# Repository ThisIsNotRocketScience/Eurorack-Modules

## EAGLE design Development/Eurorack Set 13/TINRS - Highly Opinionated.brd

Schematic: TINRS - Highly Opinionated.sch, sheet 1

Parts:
C1, C9, C15, C16, C20, C23, C24, C25, C26, C27: 3.3nF; C0603
C17, C22, C28: 100nF; C0603; MPN MC0603F104Z160CT
D5: yellow; 3MMLED
IC2, IC4, IC5: MCP6004; SO14; MPN MCP6004-I/SL.
J1, J2, J3, J4, J5, J6, J9, J15, J16, J17, J18, J19: PJ-341; 3.5MM-JACK-SWITCH-13MM-INPUT
Q1, Q2: MMBT3904; SOT23-BEC; MPN PMBT3904,215
R1, R11, R13, R14, R16, R18, R65, R76, R81, R86, R91, R96: 100k; R0603
R2, R12, R22, R23, R27, R30, R39, R41, R66, R72, R75, R82, R84, R87, R89, R92, R94, R97, R99: 33k; R0603
R3, R15, R28, R40, R71, R77, R83, R88, R93, R98: 51k; R0603
R17, R29, R68, R69, R70, R73, R85, R90, R95: 10kB; ALPS_POT_SQUAREHOLES
R20, R42: 10k; R0603
R74: 56; R0603

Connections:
3.3V: C17.1, C22.1, C28.1, IC2.4 (V+), IC4.4 (V+), IC5.4 (V+), R17.P$3 (A), R20.2, R29.P$3 (A), R42.2, R68.P$3 (A), R69.P$3 (A), R70.P$3 (A), R73.P$3 (A), R85.P$3 (A), R90.P$3 (A), R95.P$3 (A); also elsewhere on the board
12V: J9.SWITCH@3 (SWITCH); also elsewhere on the board
ADC_ATTACK: C9.2, IC4.7 (OUT), R66.1
ADC_CURVE: C20.2, IC2.1 (OUT), R39.1
ADC_CVADJUST: C24.2, C25.2, C26.2, C27.2, IC5.1 (OUT), IC5.7 (OUT), IC5.8 (OUT), IC5.14 (OUT), R82.1, R87.1, R92.1, R97.1
ADC_DECAY: C16.2, IC4.14 (OUT), R22.1
ADC_RELEASE: C1.2, IC4.1 (OUT), R2.1
ADC_SUSTAIN: C15.2, IC4.8 (OUT), R12.1
ADC_VELOCITY: C23.2, IC2.8 (OUT), R75.1
EXTCV: J16.SWITCH@3 (SWITCH); also elsewhere on the board
EXTGATE: J5.SWITCH@3 (SWITCH); also elsewhere on the board
GND: C17.2, C22.2, C28.2, D5.-, IC2.3 (+IN), IC2.10 (+IN), IC2.11 (V-), IC2.12 (+IN), IC4.3 (+IN), IC4.5 (+IN), IC4.10 (+IN), IC4.11 (V-), IC4.12 (+IN), IC5.3 (+IN), IC5.5 (+IN), IC5.10 (+IN), IC5.11 (V-), IC5.12 (+IN), J1.RING@3 (RING), J1.SWITCH@3 (SWITCH), J2.RING@3 (RING), J2.SWITCH@3 (SWITCH), J3.RING@3 (RING), J3.SWITCH@3 (SWITCH), J4.RING@3 (RING), J4.SWITCH@3 (SWITCH), J5.RING@3 (RING), J6.RING@3 (RING), J6.SWITCH@3 (SWITCH), J9.RING@3 (RING), J15.RING@3 (RING), J15.SWITCH@3 (SWITCH), J16.RING@3 (RING), J17.RING@3 (RING), J17.SWITCH@3 (SWITCH), J18.RING@3 (RING), J18.SWITCH@3 (SWITCH), J19.RING@3 (RING), J19.SWITCH@3 (SWITCH), Q1.E, Q2.E, R17.P$1 (E), R29.P$1 (E), R68.P$1 (E), R69.P$1 (E), R70.P$1 (E), R73.P$1 (E), R85.P$1 (E), R90.P$1 (E), R95.P$1 (E); also elsewhere on the board
KNOB_ATTACK: R72.2, R73.P$2 (S)
KNOB_CURVE: R41.2, R70.P$2 (S)
KNOB_CVADJUST: R29.P$2 (S), R84.2
KNOB_DECAY: R17.P$2 (S), R30.2
KNOB_INSTRUMENT: R95.P$2 (S), R99.2
KNOB_PERSONALITY: R85.P$2 (S), R89.2
KNOB_RELEASE: R27.2, R69.P$2 (S)
KNOB_SKILL: R90.P$2 (S), R94.2
KNOB_SUSTAIN: R23.2, R68.P$2 (S)
unnamed: J2.TIP@3 (TIP), R16.2
unnamed: C15.1, IC4.9 (-IN), R12.2, R15.1, R16.1, R23.1
unnamed: J3.TIP@3 (TIP), R1.2
unnamed: C1.1, IC4.2 (-IN), R1.1, R2.2, R3.1, R27.1
unnamed: J16.TIP@3 (TIP), R81.2
unnamed: C24.1, IC5.2 (-IN), R81.1, R82.2, R83.1, R84.1
unnamed: J15.TIP@3 (TIP), R65.2
unnamed: J4.TIP@3 (TIP), R13.2
unnamed: Q1.B, R18.2
unnamed: J5.TIP@3 (TIP), R18.1
unnamed: IC2.6 (-IN), IC2.7 (OUT), R74.2
unnamed: C9.1, IC4.6 (-IN), R65.1, R66.2, R71.1, R72.1
unnamed: IC2.13 (-IN), IC2.14 (OUT)
unnamed: J1.TIP@3 (TIP), R14.2
unnamed: C16.1, IC4.13 (-IN), R14.1, R22.2, R28.1, R30.1
unnamed: Q2.B, R11.2
unnamed: C20.1, IC2.2 (-IN), R13.1, R39.2, R40.1, R41.1
unnamed: J6.TIP@3 (TIP), R11.1
unnamed: C23.1, IC2.9 (-IN), R75.2, R76.1, R77.1
unnamed: D5.+, R74.1
unnamed: J17.TIP@3 (TIP), R86.2
unnamed: J9.TIP@3 (TIP), R76.2
unnamed: C25.1, IC5.6 (-IN), R86.1, R87.2, R88.1, R89.1
unnamed: J18.TIP@3 (TIP), R91.2
unnamed: C26.1, IC5.9 (-IN), R91.1, R92.2, R93.1, R94.1
unnamed: J19.TIP@3 (TIP), R96.2
unnamed: C27.1, IC5.13 (-IN), R96.1, R97.2, R98.1, R99.1
OUT_CUR_PRERES: IC2.5 (+IN); also elsewhere on the board
REF_-5V: R3.2, R15.2, R28.2, R40.2, R71.2, R77.2, R83.2, R88.2, R93.2, R98.2; also elsewhere on the board
RETRIGGER_ENVELOPE: Q2.C, R42.1
TRIGGER_ENVELOPE: Q1.C, R20.1

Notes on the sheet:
-5.0 to 5.0 -> 3.3 -> 0.0

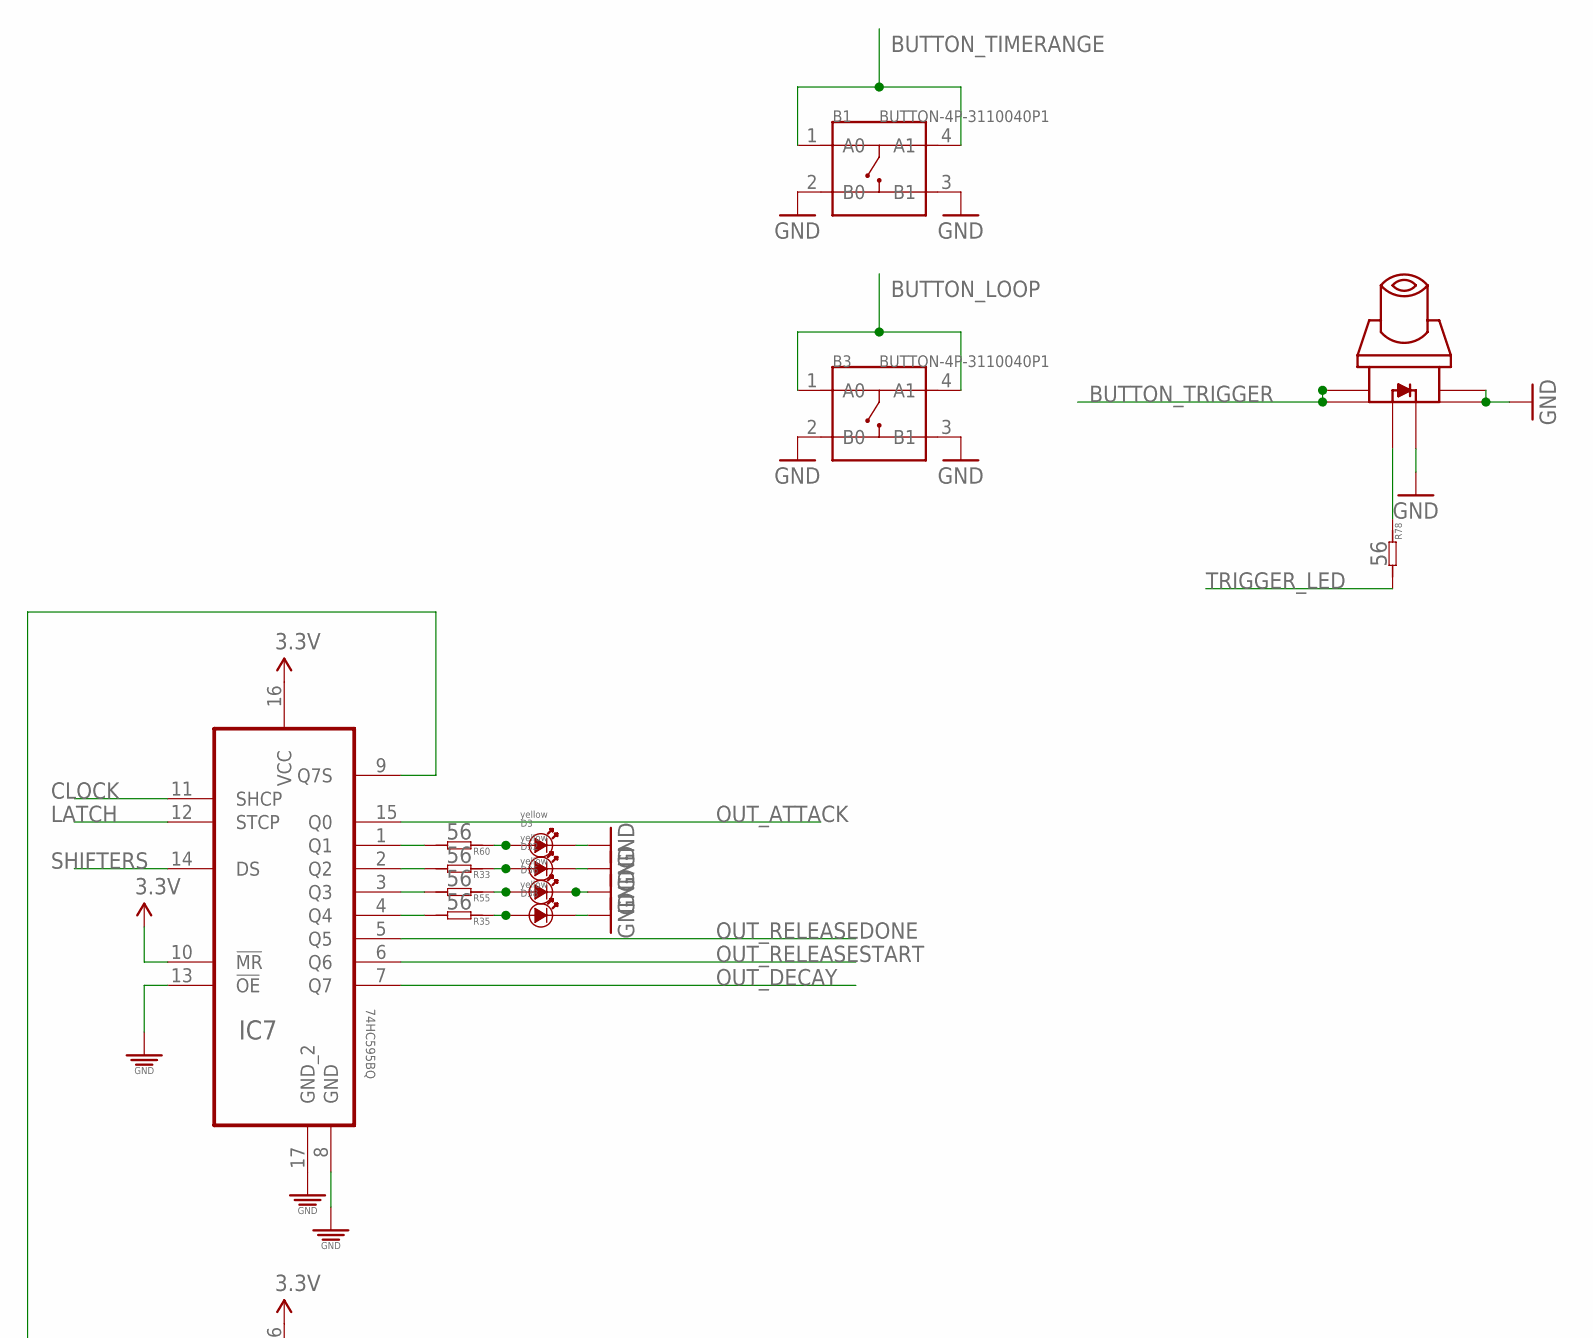
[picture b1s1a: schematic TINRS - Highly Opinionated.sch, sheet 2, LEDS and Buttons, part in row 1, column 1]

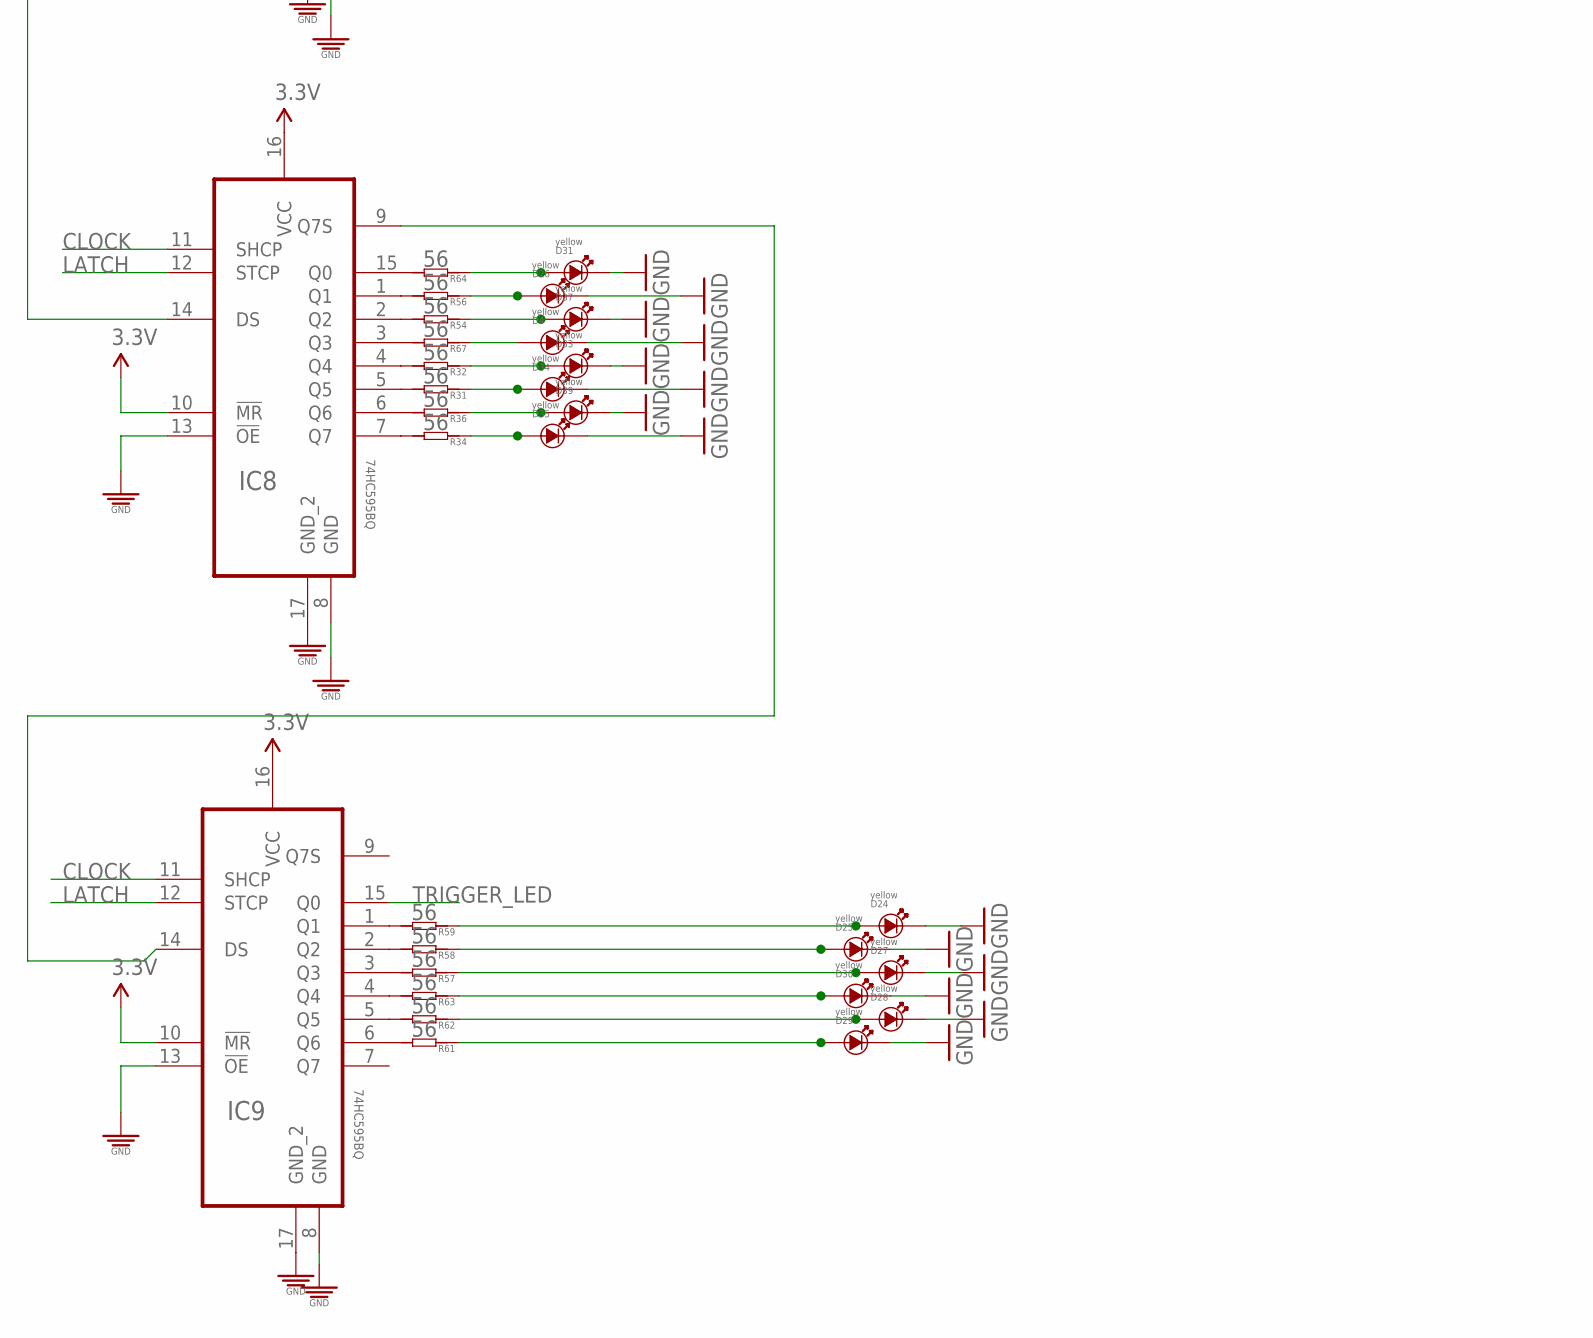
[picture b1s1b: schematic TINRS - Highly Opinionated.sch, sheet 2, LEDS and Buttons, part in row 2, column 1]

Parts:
B1, B3: BUTTON-4P-3110040P1; 4P-6.0X6.0X5.0H
D3, D4, D24, D25, D26, D27, D28, D29, D30, D31, D32, D33, D34, D35, D36, D37, D38, D39: yellow; 3MMLED
IC7, IC8, IC9: 74HC595BQ; QFN50P250X350X100-17N
R31, R32, R33, R34, R35, R36, R54, R55, R56, R57, R58, R59, R60, R61, R62, R63, R64, R67, R78: 56; R0603
U$2: SWITCH_W_LED_PB6149L-X-102YELLOW; PB6149L

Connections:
3.3V: IC7.10 (!MR), IC7.16 (VCC), IC8.10 (!MR), IC8.16 (VCC), IC9.10 (!MR), IC9.16 (VCC); also elsewhere on the board
BUTTON_LOOP: B3.1 (A0), B3.4 (A1)
BUTTON_TIMERANGE: B1.1 (A0), B1.4 (A1)
BUTTON_TRIGGER: U$2.1, U$2.2
CLOCK: IC7.11 (SHCP), IC8.11 (SHCP), IC9.11 (SHCP)
GND: B1.2 (B0), B1.3 (B1), B3.2 (B0), B3.3 (B1), D3.-, D4.-, D24.-, D25.-, D26.-, D27.-, D28.-, D29.-, D30.-, D31.-, D32.-, D33.-, D34.-, D35.-, D36.-, D37.-, D38.-, D39.-, IC7.8 (GND), IC7.13 (!OE), IC7.17 (GND_2), IC8.8 (GND), IC8.13 (!OE), IC8.17 (GND_2), IC9.8 (GND), IC9.13 (!OE), IC9.17 (GND_2), U$2.3, U$2.4, U$2.LEDNEG (NEG); also elsewhere on the board
LATCH: IC7.12 (STCP), IC8.12 (STCP), IC9.12 (STCP)
unnamed: R78.1, U$2.LEDPOS (POS)
unnamed: IC8.7 (Q7), R34.2
unnamed: IC8.15 (Q0), R64.2
unnamed: D28.+, R62.1
unnamed: D4.+, R67.1
unnamed: IC7.1 (Q1), R60.2
unnamed: D29.+, R61.1
unnamed: IC7.2 (Q2), R33.2
unnamed: IC7.3 (Q3), R55.2
unnamed: IC7.4 (Q4), R35.2
unnamed: IC8.1 (Q1), R56.2
unnamed: IC8.2 (Q2), R54.2
unnamed: IC8.3 (Q3), R67.2
unnamed: IC8.4 (Q4), R32.2
unnamed: IC8.5 (Q5), R31.2
unnamed: IC8.6 (Q6), R36.2
unnamed: IC9.1 (Q1), R59.2
unnamed: IC9.2 (Q2), R58.2
unnamed: D3.+, R60.1
unnamed: IC9.3 (Q3), R57.2
unnamed: IC9.4 (Q4), R63.2
unnamed: IC9.5 (Q5), R62.2
unnamed: IC9.6 (Q6), R61.2
unnamed: D27.+, R57.1
unnamed: D26.+, R56.1
unnamed: D25.+, R58.1
unnamed: D24.+, R59.1
unnamed: D30.+, R63.1
unnamed: D31.+, R64.1
unnamed: D32.+, R33.1
unnamed: D33.+, R32.1
unnamed: D34.+, R31.1
unnamed: D35.+, R34.1
unnamed: D36.+, R55.1
unnamed: D37.+, R54.1
unnamed: D38.+, R35.1
unnamed: D39.+, R36.1
OUT_ATTACK: IC7.15 (Q0); also elsewhere on the board
OUT_DECAY: IC7.7 (Q7); also elsewhere on the board
OUT_RELEASEDONE: IC7.5 (Q5); also elsewhere on the board
OUT_RELEASESTART: IC7.6 (Q6); also elsewhere on the board
SHIFTER1TO2: IC7.9 (Q7S), IC8.14 (DS)
SHIFTER2TO3: IC8.9 (Q7S), IC9.14 (DS)
SHIFTERS: IC7.14 (DS)
TRIGGER_LED: IC9.15 (Q0), R78.2

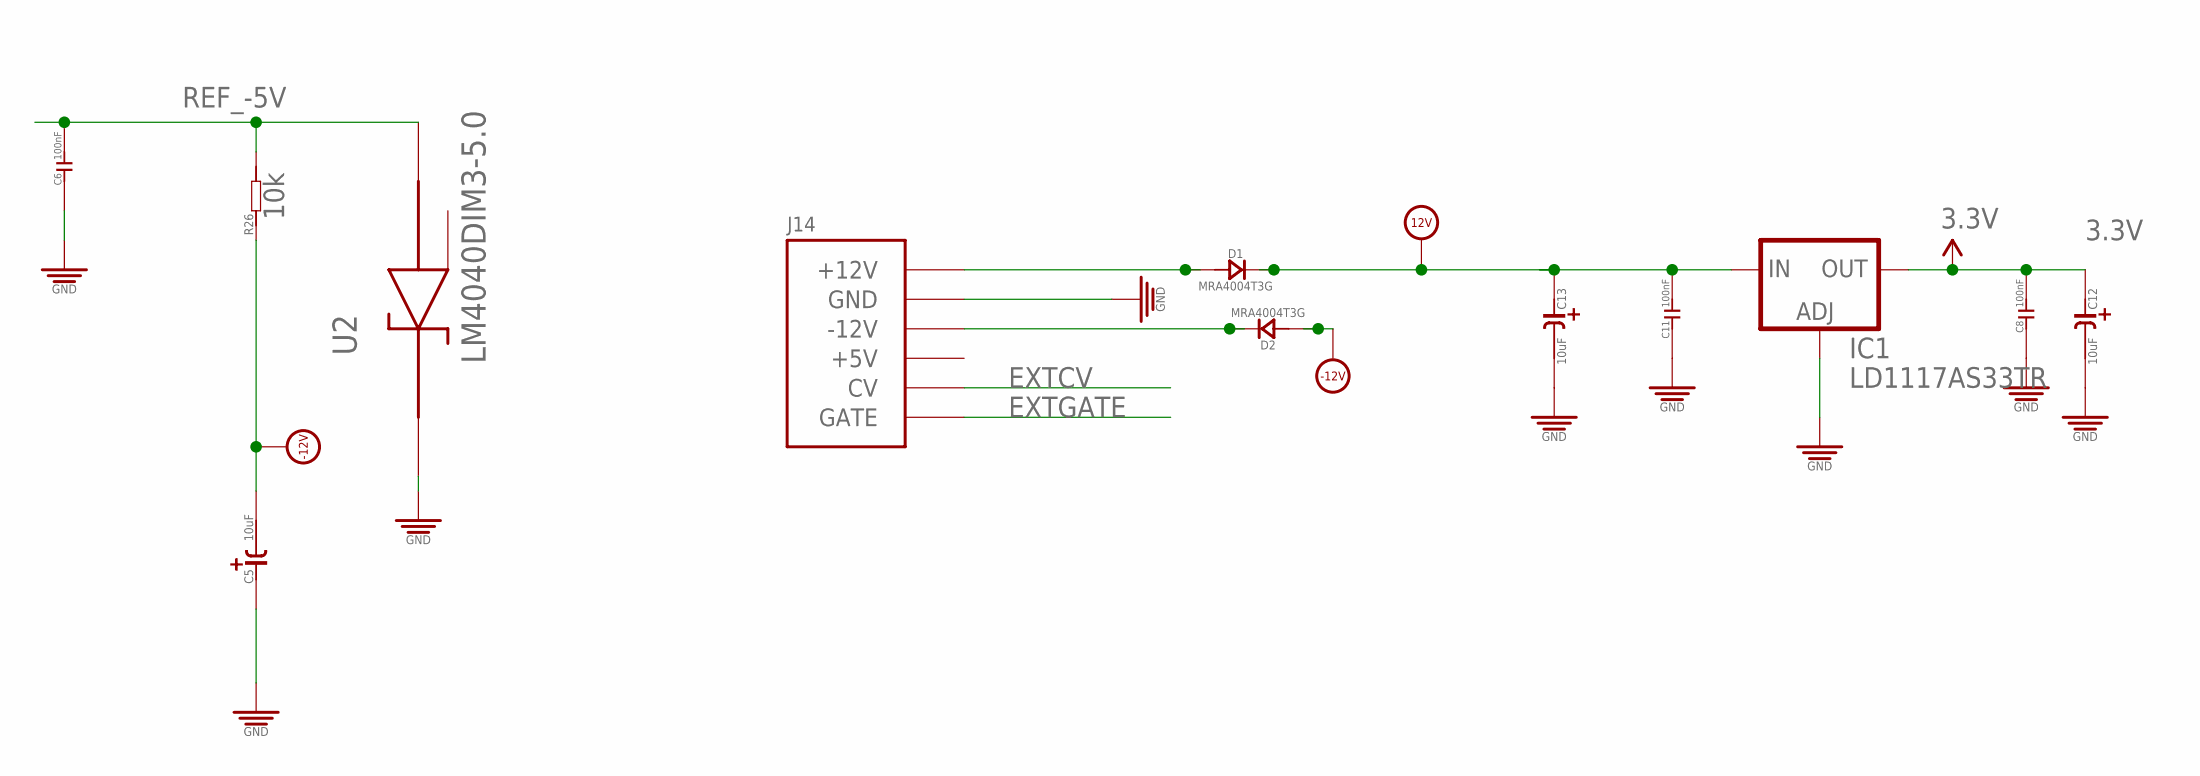
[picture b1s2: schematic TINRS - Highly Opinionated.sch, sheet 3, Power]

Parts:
C5, C12, C13: 10uF; CASE-A_3216; MPN TAJB106K020RNJ
C6: 100nF; C0603; MPN 06035C104KAT2A
C8, C11: 100nF; C0603; MPN MC0603F104Z160CT
D1, D2: MRA4004T3G; DO-214AC; MPN US1G-E3/5AT
IC1: LD1117AS33TR; SOT223; MPN LD1117AS33TR
J14: POWERSHROUDED; POWER_16_SHROUDED
R26: 10k; R0603
U2: LM4040DIM3-5.0; SOT95P237X112-3N

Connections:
3.3V: C8.2, C12.+ (1), IC1.2 (OUT), IC1.4 (OUT); also elsewhere on the board
12V: C11.2, C13.+ (1), D1.2 (-), IC1.3 (IN); also elsewhere on the board
-12V: C5.- (2), D2.1 (+), R26.1; also elsewhere on the board
EXTCV: J14.13 (CV), J14.14 (CV); also elsewhere on the board
EXTGATE: J14.15 (GATE), J14.16 (GATE); also elsewhere on the board
GND: C5.+ (1), C6.1, C8.1, C11.1, C12.- (2), C13.- (2), IC1.1 (ADJ), J14.3 (GND), J14.4 (GND), J14.5 (GND), J14.6 (GND), J14.7 (GND), J14.8 (GND), U2.1 (CATHODE); also elsewhere on the board
unnamed: D1.1 (+), J14.9 (+12V), J14.10 (+12V)
unnamed: D2.2 (-), J14.1 (-12V), J14.2 (-12V)
REF_-5V: C6.2, R26.2, U2.2 (ANODE); also elsewhere on the board

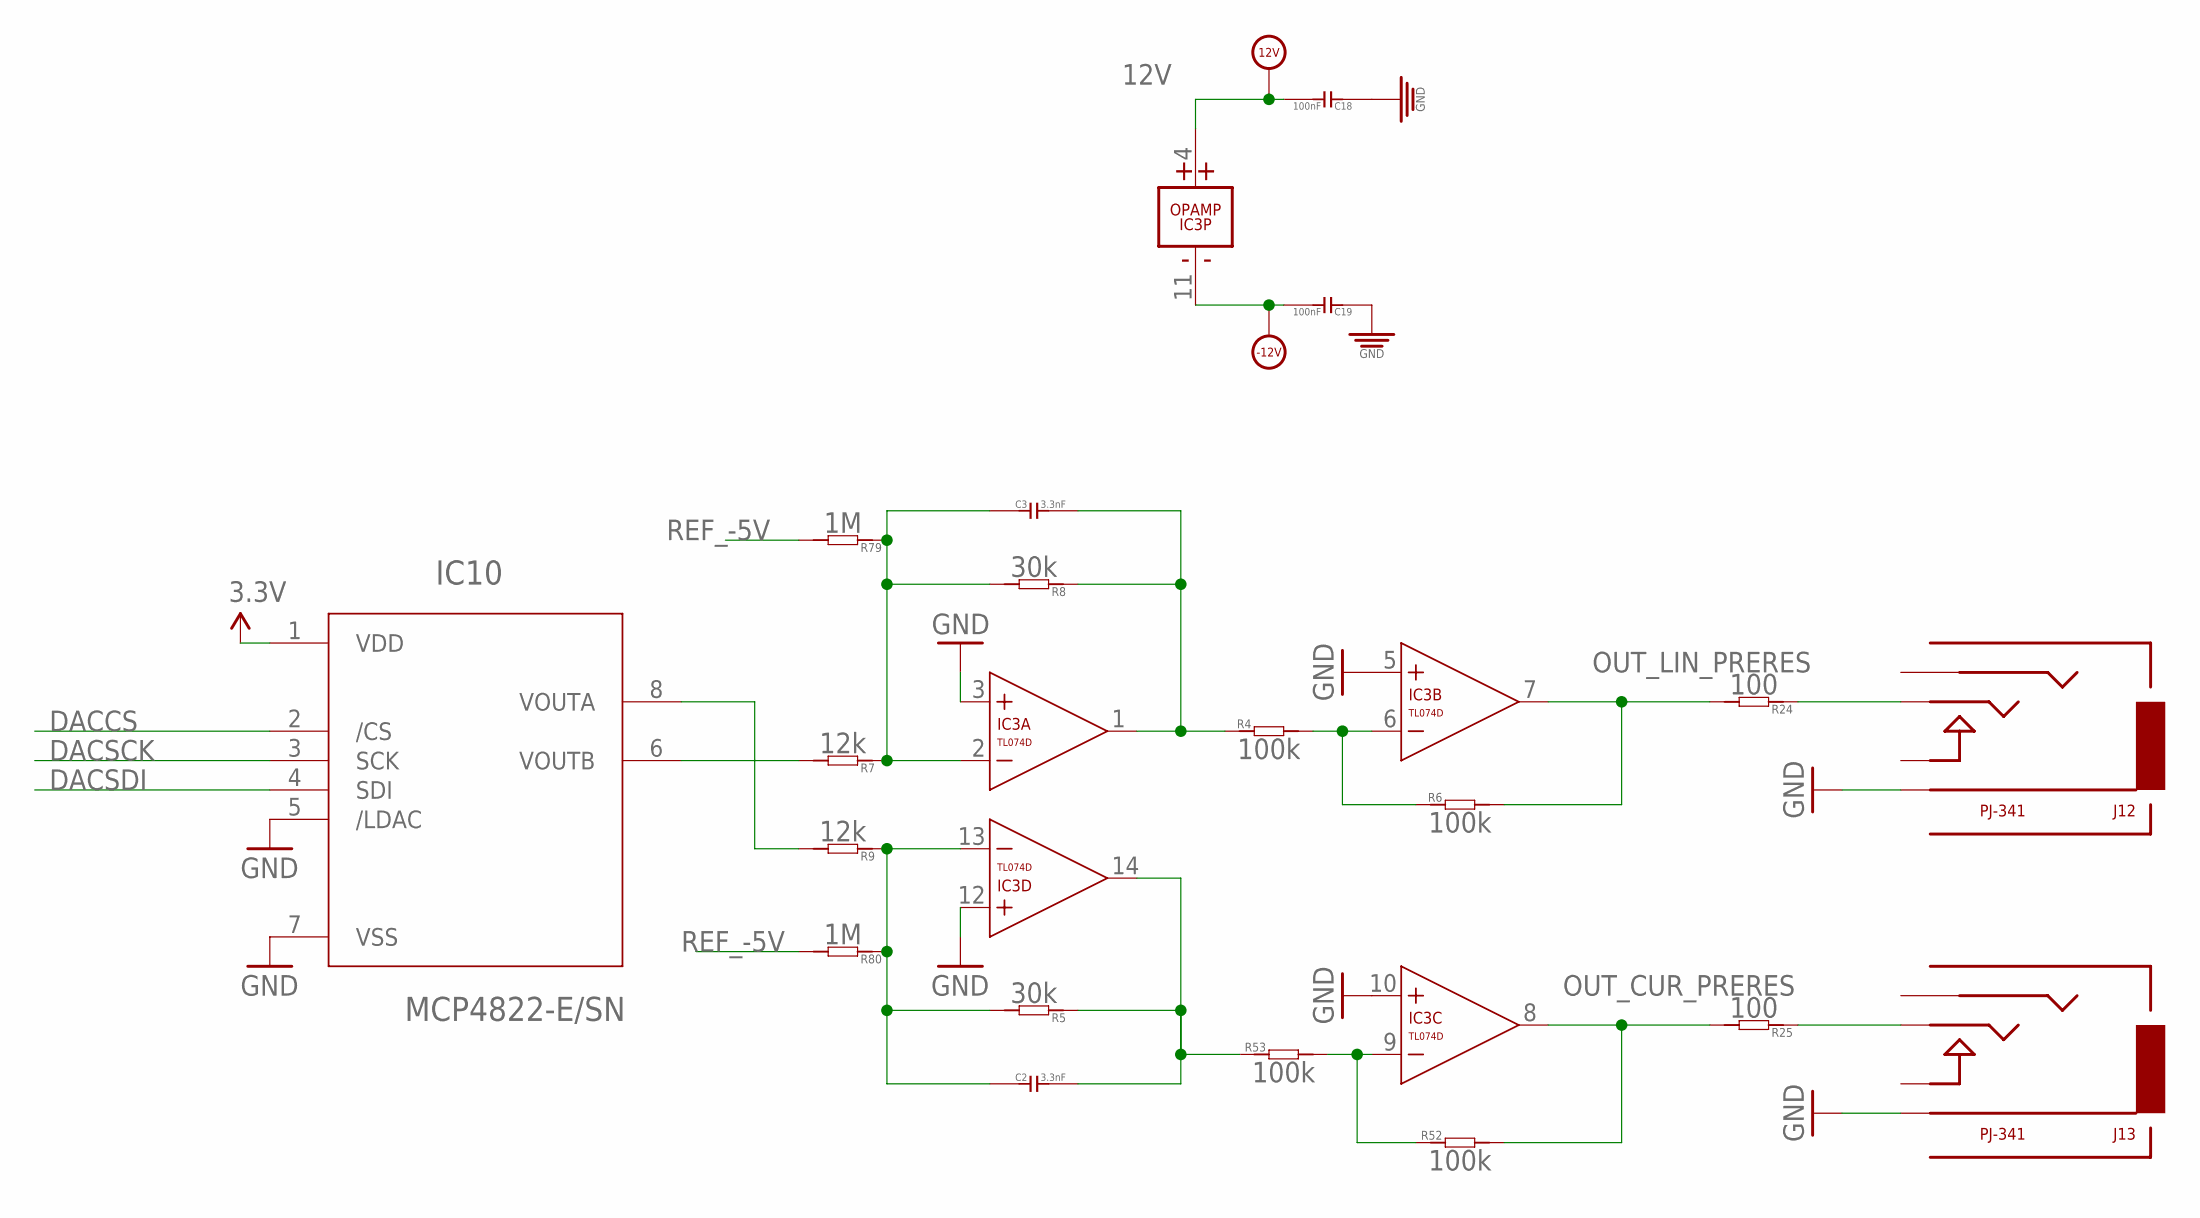
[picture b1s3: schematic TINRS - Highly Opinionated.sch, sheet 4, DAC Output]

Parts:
C2, C3: 3.3nF; C0603
C18, C19: 100nF; C0603; MPN MC0603F104Z160CT
IC3: TL074D; SO14; MPN TL074CD
IC10: MCP4822-E/SN; SOIC8-N_MC
J12, J13: PJ-341; 3.5MM-JACK-SWITCH-13MM-OUTPUT
R4, R6, R52, R53: 100k; R0603
R5, R8: 30k; R0603
R7, R9: 12k; R0603
R24, R25: 100; R0603
R79, R80: 1M; R0603

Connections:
3.3V: IC10.1 (VDD); also elsewhere on the board
12V: C18.2, IC3.4 (V+); also elsewhere on the board
-12V: C19.2, IC3.11 (V-); also elsewhere on the board
DACA_INPUTSUMMER: C2.1, IC3.13 (-IN), R5.2, R9.1, R80.1
DACB_INPUTSUMMER: C3.1, IC3.2 (-IN), R7.1, R8.2, R79.1
DACCS: IC10.2 (/CS)
DACSCK: IC10.3 (SCK)
DACSDI: IC10.4 (SDI)
GND: C18.1, C19.1, IC3.3 (+IN), IC3.5 (+IN), IC3.10 (+IN), IC3.12 (+IN), IC10.5 (/LDAC), IC10.7 (VSS), J12.RING@3 (RING), J13.RING@3 (RING); also elsewhere on the board
unnamed: IC3.6 (-IN), R4.2, R6.1
unnamed: IC10.8 (VOUTA), R9.2
unnamed: IC10.6 (VOUTB), R7.2
unnamed: IC3.9 (-IN), R52.1, R53.2
unnamed: C3.2, IC3.1 (OUT), R4.1, R8.1
unnamed: J13.TIP@3 (TIP), R25.1
unnamed: J12.TIP@3 (TIP), R24.1
unnamed: C2.2, IC3.14 (OUT), R5.1, R53.1
OUT_CUR_PRERES: IC3.8 (OUT), R25.2, R52.2; also elsewhere on the board
OUT_LIN_PRERES: IC3.7 (OUT), R6.2, R24.2
REF_-5V: R79.2, R80.2; also elsewhere on the board

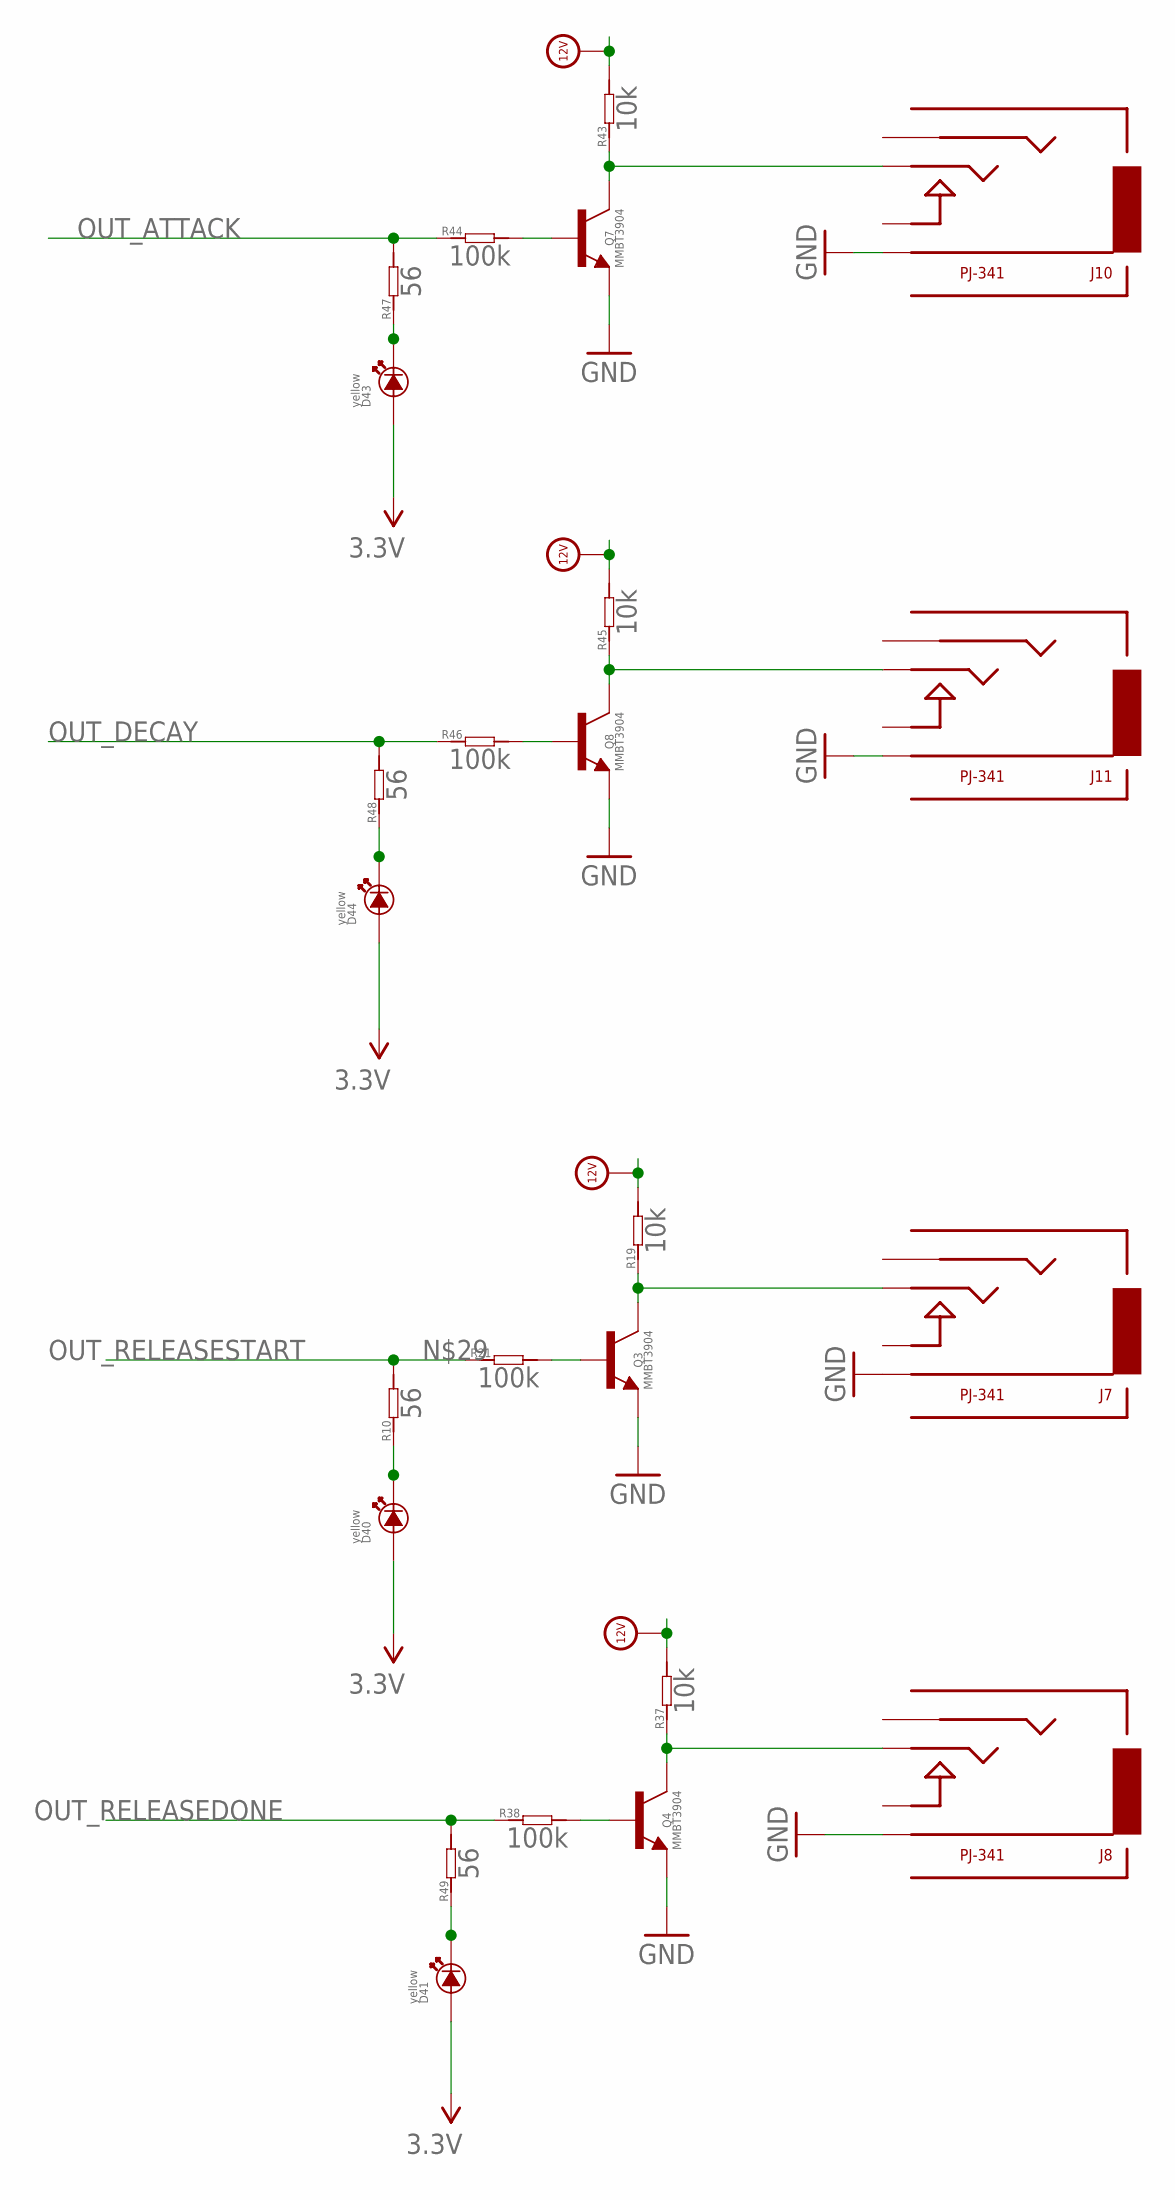
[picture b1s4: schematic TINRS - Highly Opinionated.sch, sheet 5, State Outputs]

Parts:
D40, D41, D43, D44: yellow; 3MMLED
J7, J8, J10, J11: PJ-341; 3.5MM-JACK-SWITCH-13MM-OUTPUT
Q3, Q4, Q7, Q8: MMBT3904; SOT23-BEC; MPN PMBT3904,215
R10, R47, R48, R49: 56; R0603
R19, R37, R43, R45: 10k; R0603
R21, R38, R44, R46: 100k; R0603

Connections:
3.3V: D40.+, D41.+, D43.+, D44.+; also elsewhere on the board
12V: R19.2, R37.2, R43.2, R45.2; also elsewhere on the board
D21: D43.-, R47.1
GND: J7.RING@3 (RING), J8.RING@3 (RING), J10.RING@3 (RING), J11.RING@3 (RING), Q3.E, Q4.E, Q7.E, Q8.E; also elsewhere on the board
unnamed: D40.-, R10.1
unnamed: Q3.B, R21.2
unnamed: J7.TIP@3 (TIP), Q3.C, R19.1
unnamed: D41.-, R49.1
unnamed: D44.-, R48.1
unnamed: Q4.B, R38.2
unnamed: J8.TIP@3 (TIP), Q4.C, R37.1
unnamed: Q7.B, R44.2
unnamed: J10.TIP@3 (TIP), Q7.C, R43.1
unnamed: Q8.B, R46.2
unnamed: J11.TIP@3 (TIP), Q8.C, R45.1
OUT_ATTACK: R44.1, R47.2; also elsewhere on the board
OUT_DECAY: R46.1, R48.2; also elsewhere on the board
OUT_RELEASEDONE: R38.1, R49.2; also elsewhere on the board
OUT_RELEASESTART: R10.2, R21.1; also elsewhere on the board

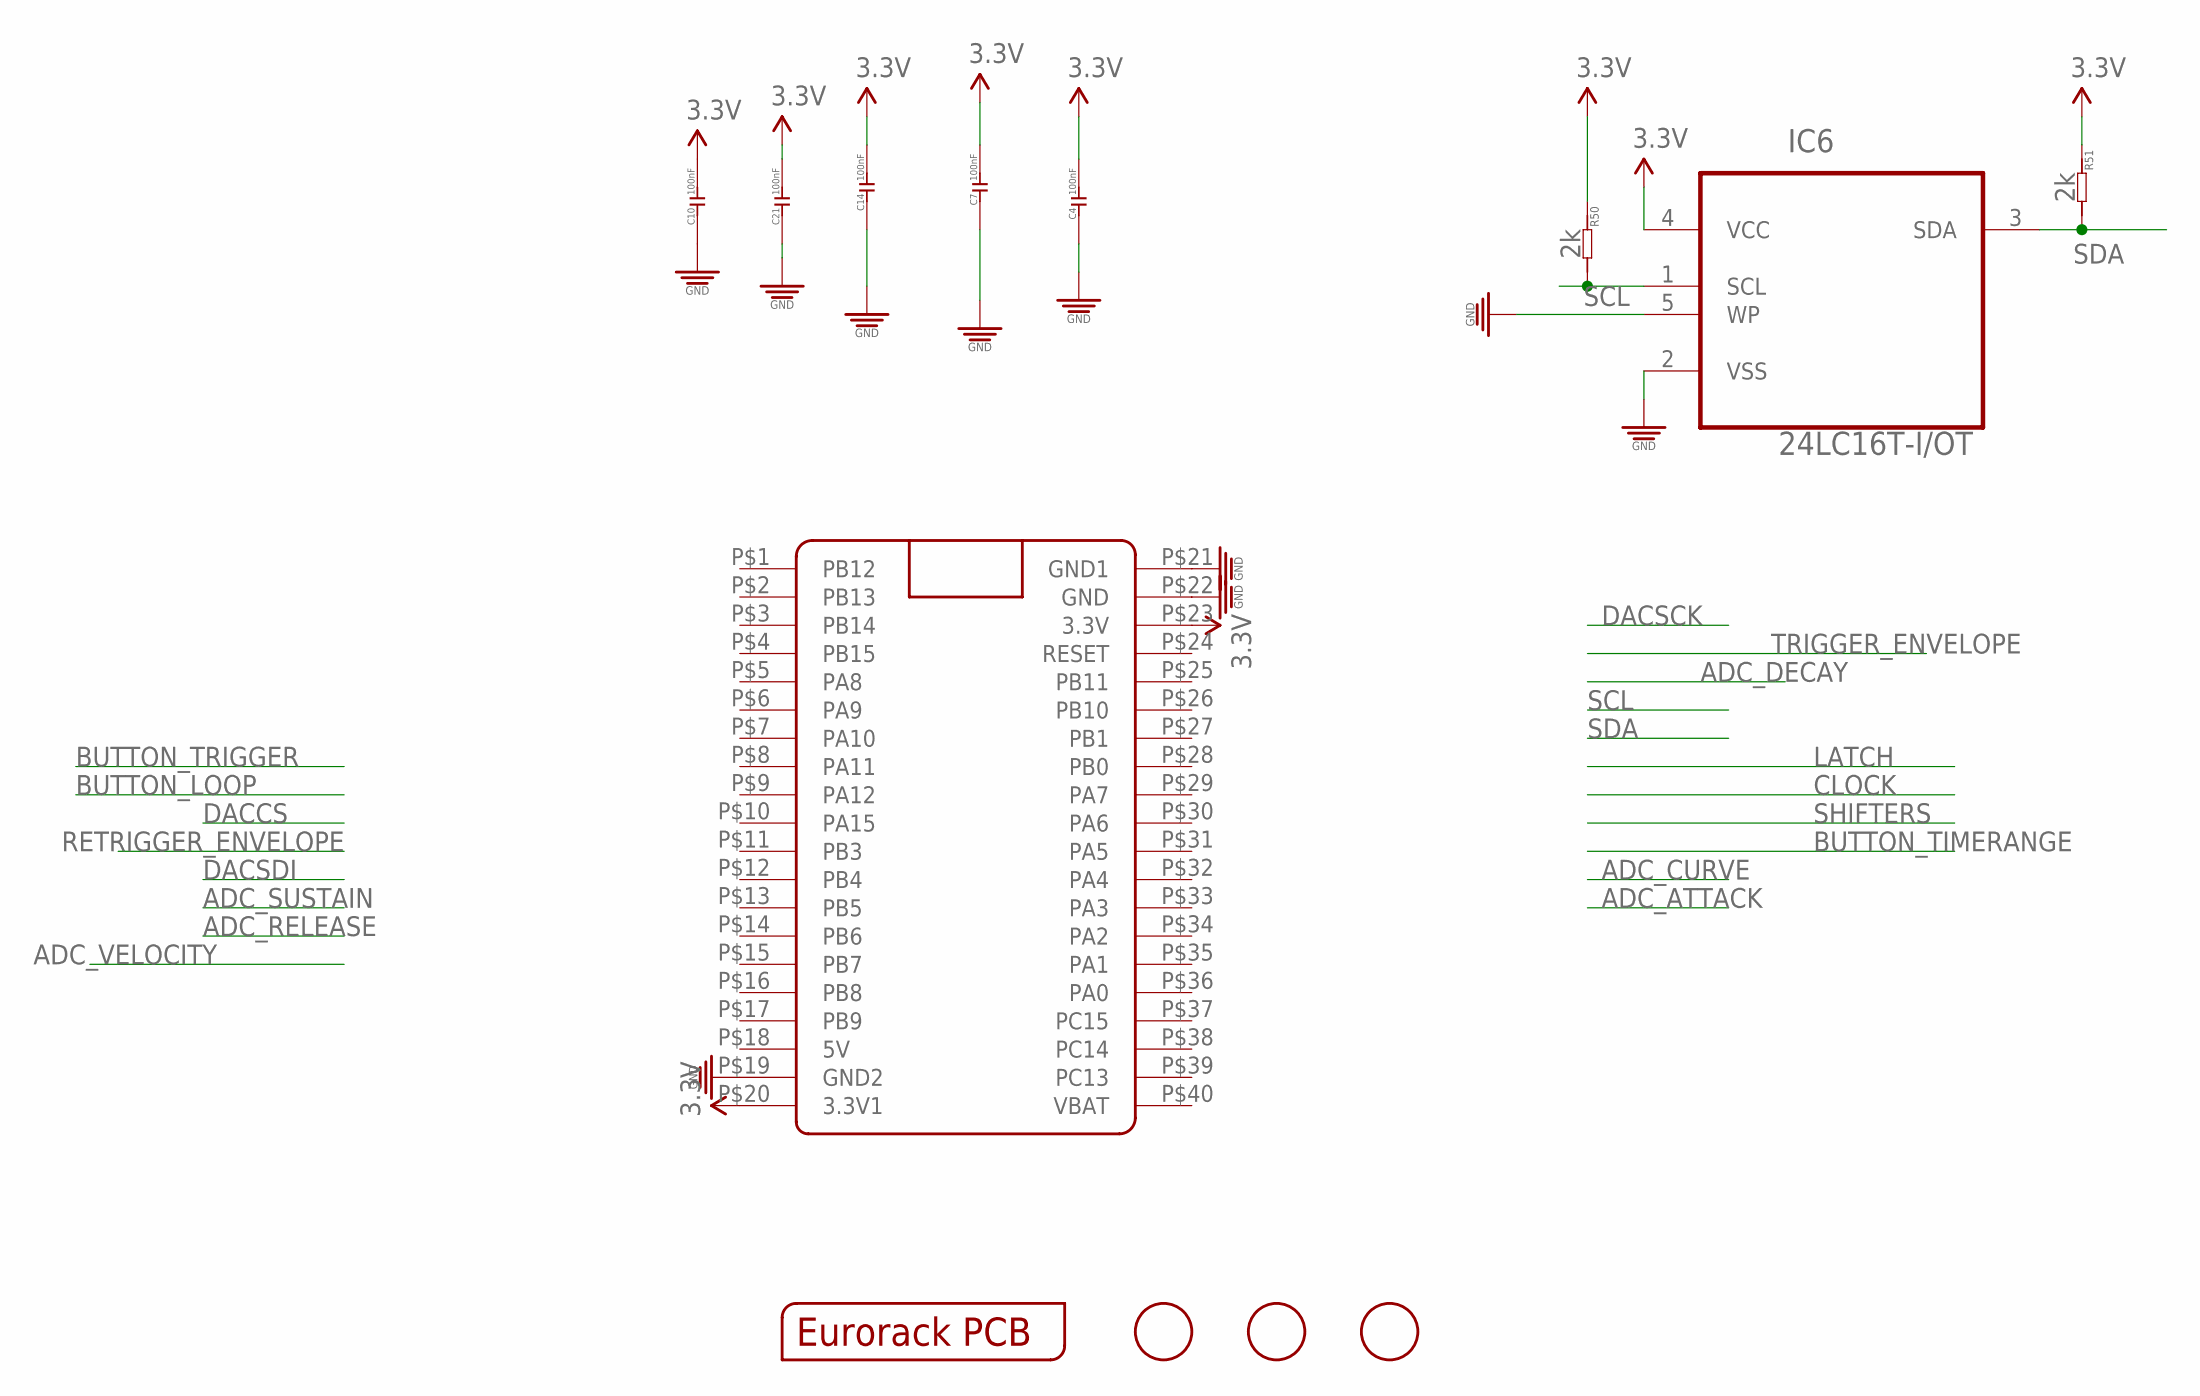
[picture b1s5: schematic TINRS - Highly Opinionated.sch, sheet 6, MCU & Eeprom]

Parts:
C4, C7, C10, C14, C21: 100nF; C0603; MPN MC0603F104Z160CT
FID1, FID2, FID3: FIDUCIAL; FIDUCIAL_1MM
IC6: 24LC16T-I/OT; SOT95P290X145-5N; MPN 24LC16T-I/OT
OUTLINE: EURORACK_PCB18HP; EURORACK18HPPCB
R50, R51: 2k; R0603
U$3: BLUE_PILL

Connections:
3.3V: C4.2, C7.2, C10.2, C14.2, C21.2, IC6.4 (VCC), R50.1, R51.1, U$3.P$20 (3.3V1), U$3.P$23 (3.3V); also elsewhere on the board
GND: C4.1, C7.1, C10.1, C14.1, C21.1, IC6.2 (VSS), IC6.5 (WP), U$3.P$19 (GND2), U$3.P$21 (GND1), U$3.P$22 (GND); also elsewhere on the board
SCL: IC6.1 (SCL), R50.2
SDA: IC6.3 (SDA), R51.2

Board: 2 copper layers, 196 parts (1 on the bottom side), 129 nets, no tracks yet.

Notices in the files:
parts and their libraries:
SparkFun-Aesthetics: Licensing: CC v3.0 Share-Alike You are welcome to use this library for commercial purposes.
